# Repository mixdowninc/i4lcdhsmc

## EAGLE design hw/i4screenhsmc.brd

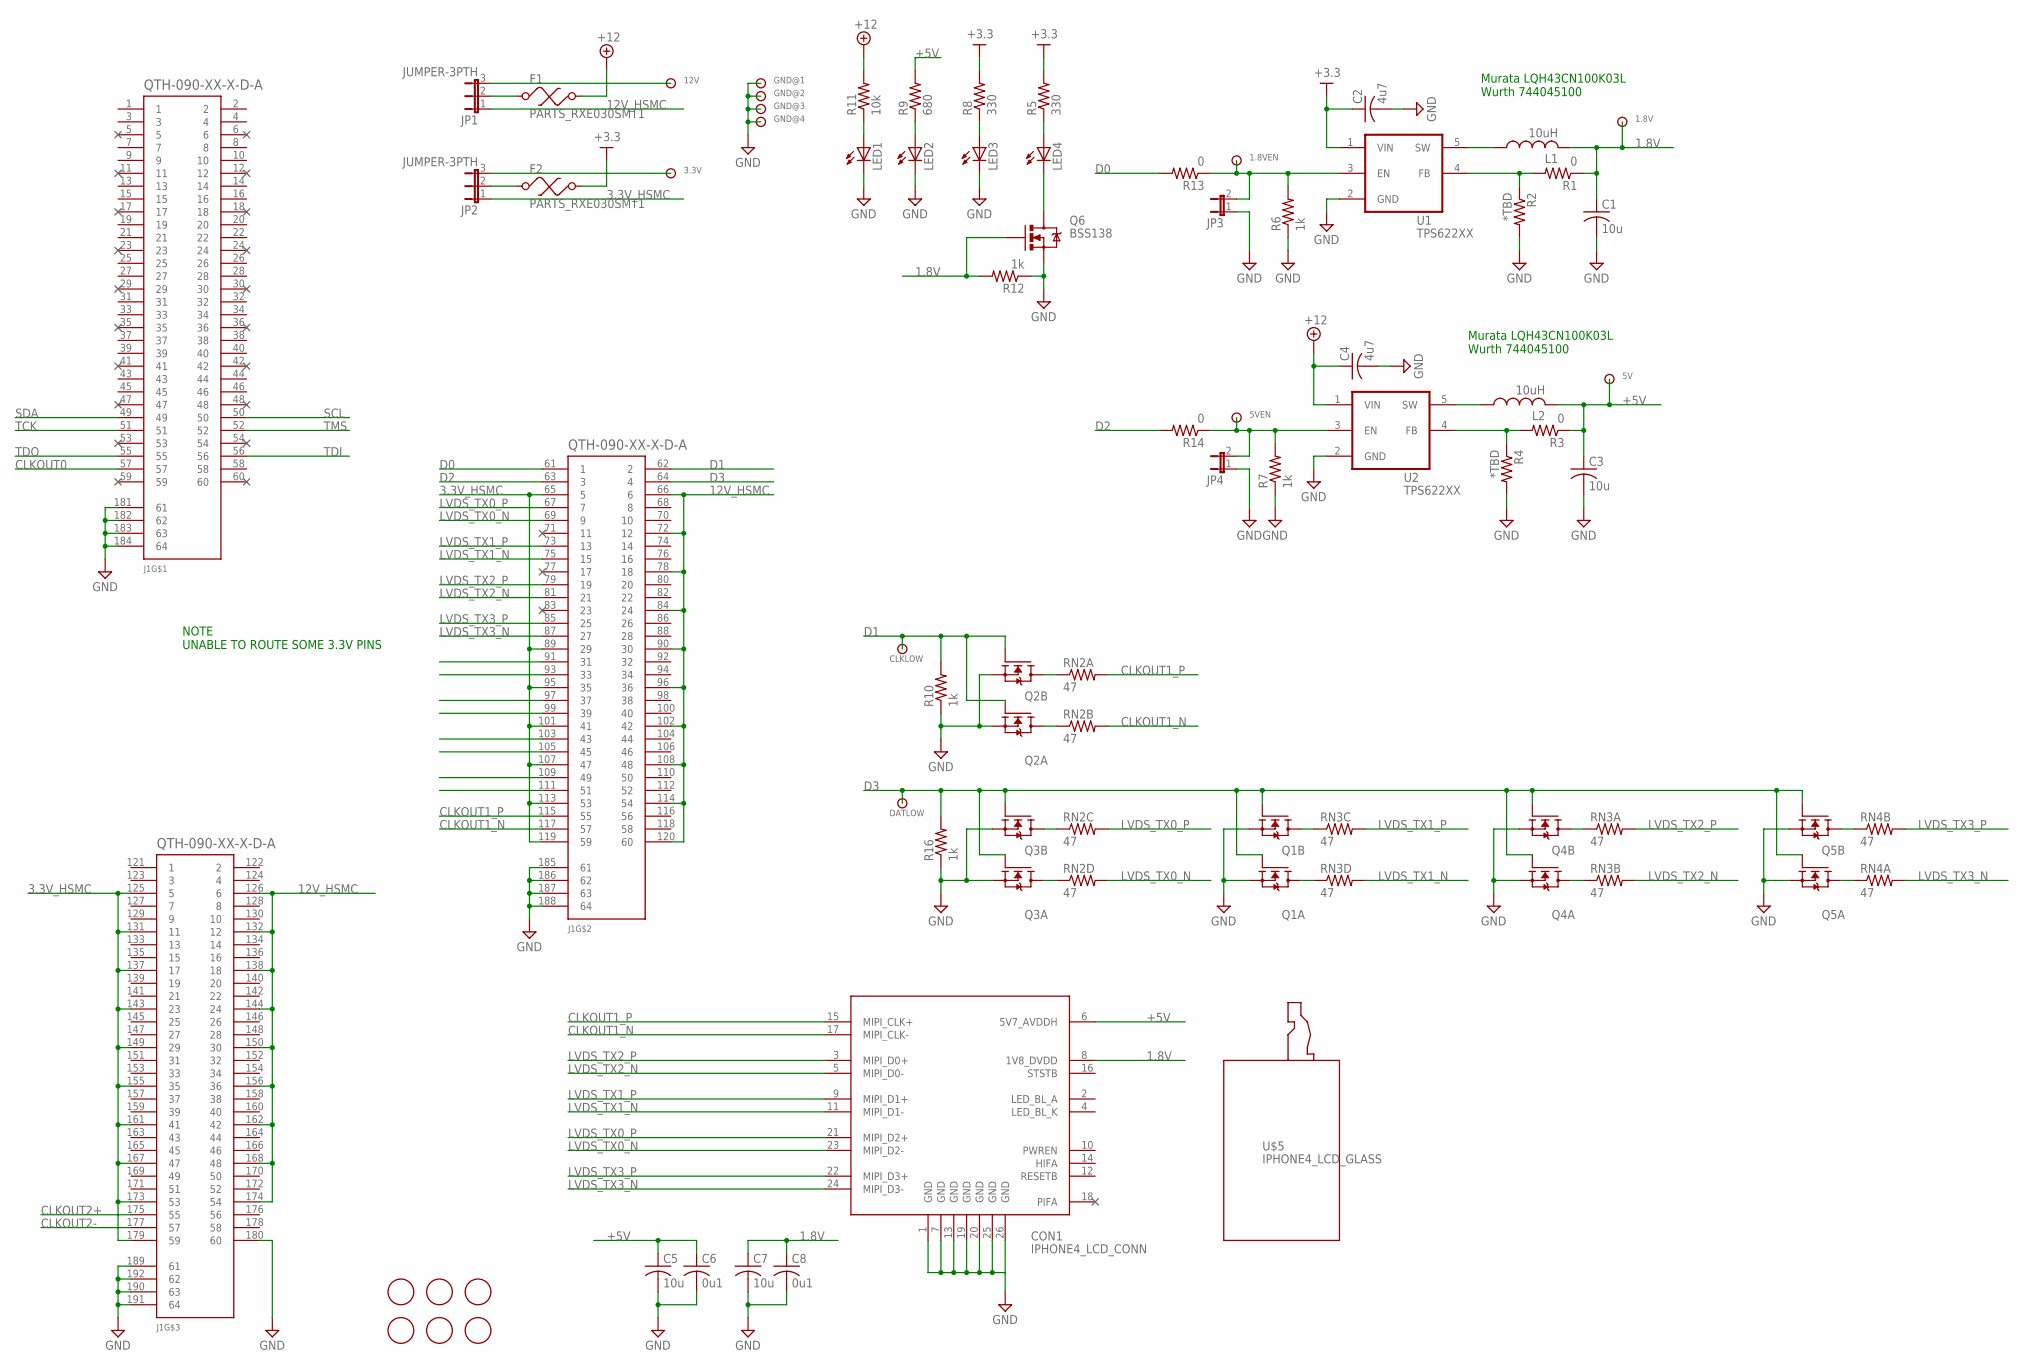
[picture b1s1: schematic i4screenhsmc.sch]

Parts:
1.8V, 5V: TESTPOINTKEYSTONE_5015; 5015
1.8VEN, 5VEN: TESTPOINTKEYSTONE_5016; 5016
3.3V, 12V: TESTPOINTBANANA_JACK; BANANA_JACK
C1, C3, C5, C7: 10u; C0805
C2, C4: 4u7; C0805
C6, C8: 0u1; C0805
CLKLOW: TESTPOINTKEYSTONE_5016; 5016
CON1: IPHONE4_LCD_CONN; AXE4E26124
DATLOW: TESTPOINTKEYSTONE_5016; 5016
F1, F2: PARTS_RXE030SMT1; POLYSWITCH_SMTSMALL
GND@1, GND@2: TESTPOINTBANANA_JACK; BANANA_JACK
GND@3, GND@4: TESTPOINTKEYSTONE_5015; 5015
J1: QTH-090-XX-X-D-A
JP1, JP2: JUMPER-3PTH; 1X03
JP3, JP4: JUMPER-2PTH; 1X02
L1, L2: 10uH; L1812
LED1, LED2, LED3, LED4: LEDCHIP-LED0805; CHIP-LED0805
Q1, Q2, Q3, Q4, Q5: 2N7002SC70-6; SC70-6
Q6: BSS138; SOT23-3
R1, R3, R13, R14: 0; R0805
R2, R4: *TBD; R0805
R5, R8: 330; R0805
R6, R7, R10, R12, R16: 1k; R0805
R9: 680; R0805
R11: 10k; R0805
RN2, RN3, RN4: 47; 2008
U1, U2: TPS622XX; SOT23-5
U$1, U$2, U$3, U$4, U$48, U$49: MOUNTING_HOLE125; HOLE_MTG_125
U$5: IPHONE4_LCD_GLASS; IPHONE4_LCD

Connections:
1.8V: 1.8V.P$1, C1.1, C7.1, C8.1, CON1.8 (1V8_DVDD), L1.2, Q6.1 (G), R1.1, R12.2
3.3V_HSMC: J1.65 (5), J1.89 (29), J1.95 (35), J1.101 (41), J1.107 (47), J1.113 (53), J1.119 (59), J1.125 (5), J1.131 (11), J1.137 (17), J1.143 (23), J1.149 (29), J1.155 (35), J1.161 (41), J1.167 (47), J1.173 (53), J1.179 (59), JP2.1
5VEN: 5VEN.P$1, JP4.2, R7.2, R14.1, U2.3 (EN)
12V_HSMC: J1.66 (6), J1.72 (12), J1.78 (18), J1.84 (24), J1.90 (30), J1.96 (36), J1.102 (42), J1.108 (48), J1.114 (54), J1.120 (60), J1.126 (6), J1.132 (12), J1.138 (18), J1.144 (24), J1.150 (30), J1.156 (36), J1.162 (42), J1.168 (48), J1.174 (54), JP1.1
+3.3: C2.1, F2.P$2 (2), R5.2, R8.2, U1.1 (VIN)
+5V: 5V.P$1, C3.1, C5.1, C6.1, CON1.6 (5V7_AVDDH), L2.2, R3.1, R9.2
+12: C4.1, F1.P$2 (2), R11.2, U2.1 (VIN)
CLKOUT0: J1.57
CLKOUT1_N: CON1.17 (MIPI_CLK-), J1.117 (57), RN2.7 (2)
CLKOUT1_P: CON1.15 (MIPI_CLK+), J1.115 (55), RN2.8 (2)
CLKOUT2+: J1.175 (55)
CLKOUT2-: J1.177 (57)
D0: J1.61 (1), R13.2
D1: CLKLOW.P$1, J1.62 (2), Q2.2 (G), Q2.5 (G), R10.2
D2: J1.63 (3), R14.2
D3: DATLOW.P$1, J1.64 (4), Q1.2 (G), Q1.5 (G), Q3.2 (G), Q3.5 (G), Q4.2 (G), Q4.5 (G), Q5.2 (G), Q5.5 (G), R16.2
GND: C1.2, C2.2, C3.2, C4.2, C5.2, C6.2, C7.2, C8.2, CON1.1 (GND), CON1.7 (GND), CON1.13 (GND), CON1.19 (GND), CON1.20 (GND), CON1.25 (GND), CON1.26 (GND), GND@1.1, GND@2.1, GND@3.P$1, GND@4.P$1, J1.180 (60), J1.181 (61), J1.182 (62), J1.183 (63), J1.184 (64), J1.185 (61), J1.186 (62), J1.187 (63), J1.188 (64), J1.189 (61), J1.190 (63), J1.191 (64), J1.192 (62), JP3.1, JP4.1, LED1.C, LED2.C, LED3.C, Q1.1 (S), Q1.4 (S), Q2.1 (S), Q2.4 (S), Q3.1 (S), Q3.4 (S), Q4.1 (S), Q4.4 (S), Q5.1 (S), Q5.4 (S), Q6.2 (S), R2.2, R4.2, R6.1, R7.1, R10.1, R12.1, R16.1, U1.2 (GND), U2.2 (GND)
LVDS_TX0_N: CON1.23 (MIPI_D2-), J1.69 (9), RN2.5 (2)
LVDS_TX0_P: CON1.21 (MIPI_D2+), J1.67 (7), RN2.6 (2)
LVDS_TX1_N: CON1.11 (MIPI_D1-), J1.75 (15), RN3.5 (2)
LVDS_TX1_P: CON1.9 (MIPI_D1+), J1.73 (13), RN3.6 (2)
LVDS_TX2_N: CON1.5 (MIPI_D0-), J1.81 (21), RN3.7 (2)
LVDS_TX2_P: CON1.3 (MIPI_D0+), J1.79 (19), RN3.8 (2)
LVDS_TX3_N: CON1.24 (MIPI_D3-), J1.87 (27), RN4.8 (2)
LVDS_TX3_P: CON1.22 (MIPI_D3+), J1.85 (25), RN4.7 (2)
unnamed: 1.8VEN.P$1, JP3.2, R6.2, R13.1, U1.3 (EN)
unnamed: L1.1, U1.5 (SW)
unnamed: L2.1, U2.5 (SW)
unnamed: LED4.A, R5.1
unnamed: Q1.6 (D), RN3.3 (1)
unnamed: F2.P$1 (1), JP2.2
unnamed: Q1.3 (D), RN3.4 (1)
unnamed: Q2.6 (D), RN2.1
unnamed: Q2.3 (D), RN2.2 (1)
unnamed: Q3.6 (D), RN2.3 (1)
unnamed: Q3.3 (D), RN2.4 (1)
unnamed: Q4.6 (D), RN3.1
unnamed: Q4.3 (D), RN3.2 (1)
unnamed: F1.P$1 (1), JP1.2
unnamed: R1.2, R2.1, U1.4 (FB)
unnamed: Q5.6 (D), RN4.2 (1)
unnamed: Q5.3 (D), RN4.1
unnamed: R3.2, R4.1, U2.4 (FB)
unnamed: 12V.1, JP1.3
unnamed: 3.3V.1, JP2.3
unnamed: LED3.A, R8.1
unnamed: LED2.A, R9.1
unnamed: LED1.A, R11.1
unnamed: LED4.C, Q6.3 (D)
SCL: J1.50
SDA: J1.49
TCK: J1.51
TDI: J1.56
TDO: J1.55
TMS: J1.52

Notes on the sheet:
Murata LQH43CN100K03L Wurth 744045100
NOTE UNABLE TO ROUTE SOME 3.3V PINS

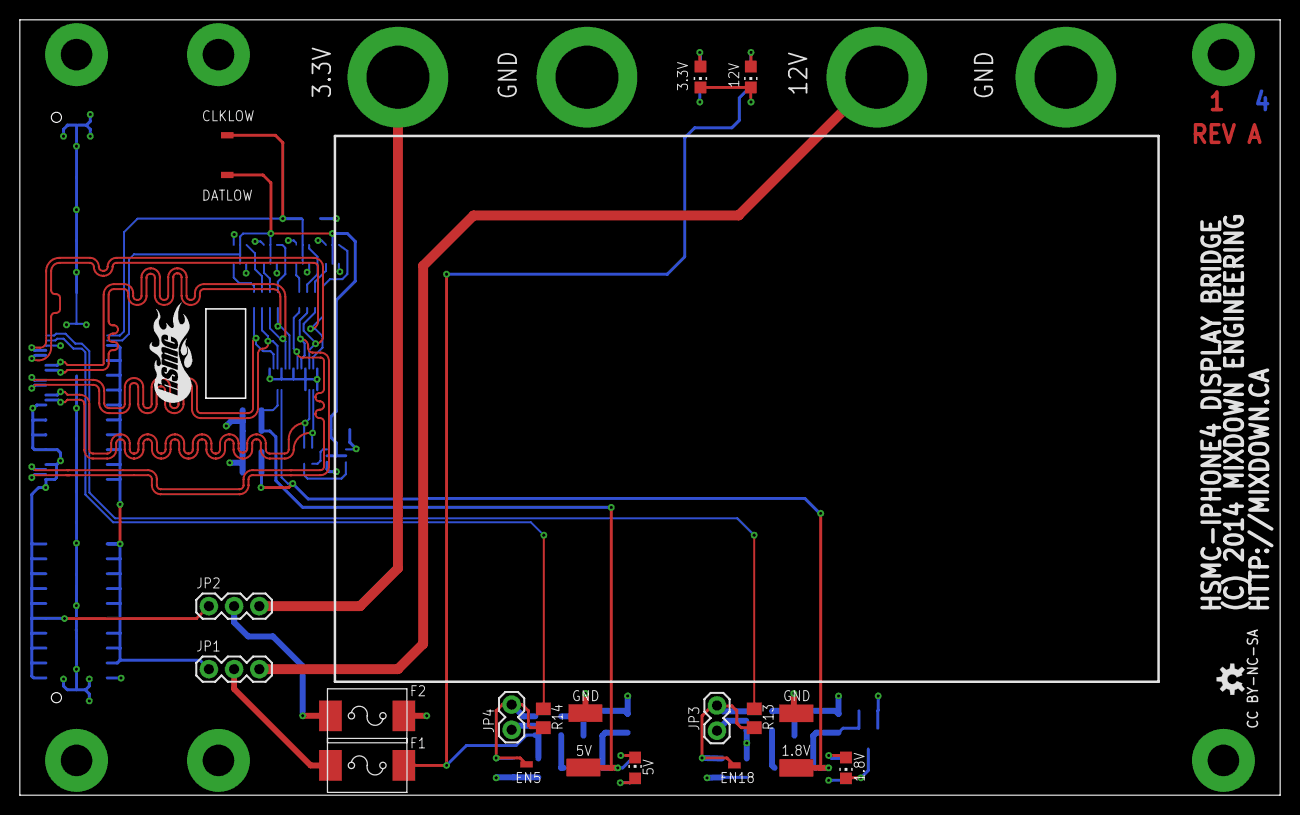
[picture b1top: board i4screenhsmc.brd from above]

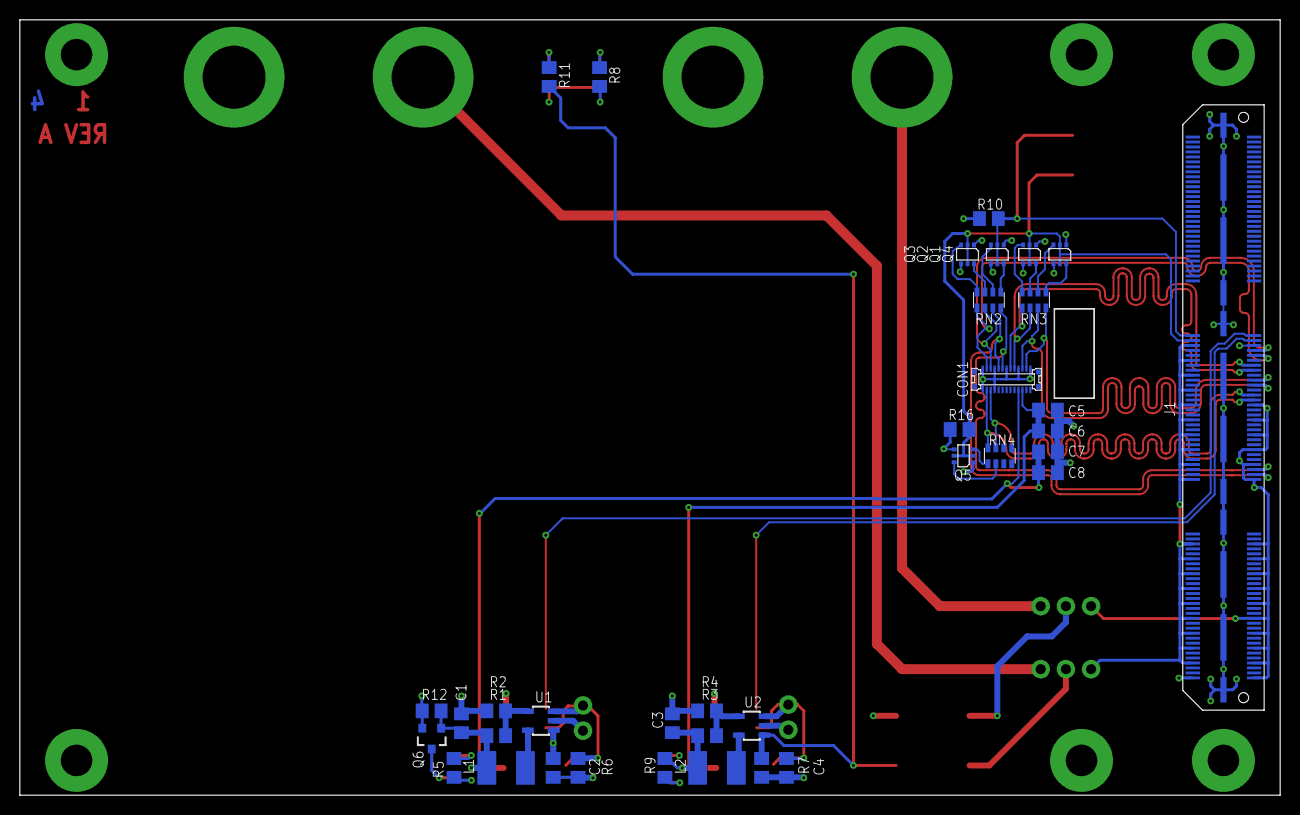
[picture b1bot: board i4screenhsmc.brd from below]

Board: 4 copper layers, 126.8 x 78.0 mm, 67 parts (36 on the bottom side), 46 nets.

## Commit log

2014-02-28 initial design
2014-03-02 move hardware to hw directory
2014-03-02 make MIPI traces 8mil wide but do not adjust spacing at all. This should be closer to 100 ohms differential, and beats ripping up all the copper and re-routing.
2014-08-26 the N-channel FET is a BSS138, not a BSS84 (which is P-channel)

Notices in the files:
hw/i4screenhsmc.brd:
(C) 2014 MIXDOWN ENGINEERING
CC BY-NC-SA
parts and their libraries:
SparkFun: Licensing: CC v3.0 Share-Alike You are welcome to use this library for commercial purposes.
